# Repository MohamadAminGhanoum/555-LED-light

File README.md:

# 555-LED-light
This project is a type of LED chaser, which is LED's making spinning effect by switching on and off.  i have followed a guide on blueprint, hackclub to build this project.

I think total price is 2 dollar.

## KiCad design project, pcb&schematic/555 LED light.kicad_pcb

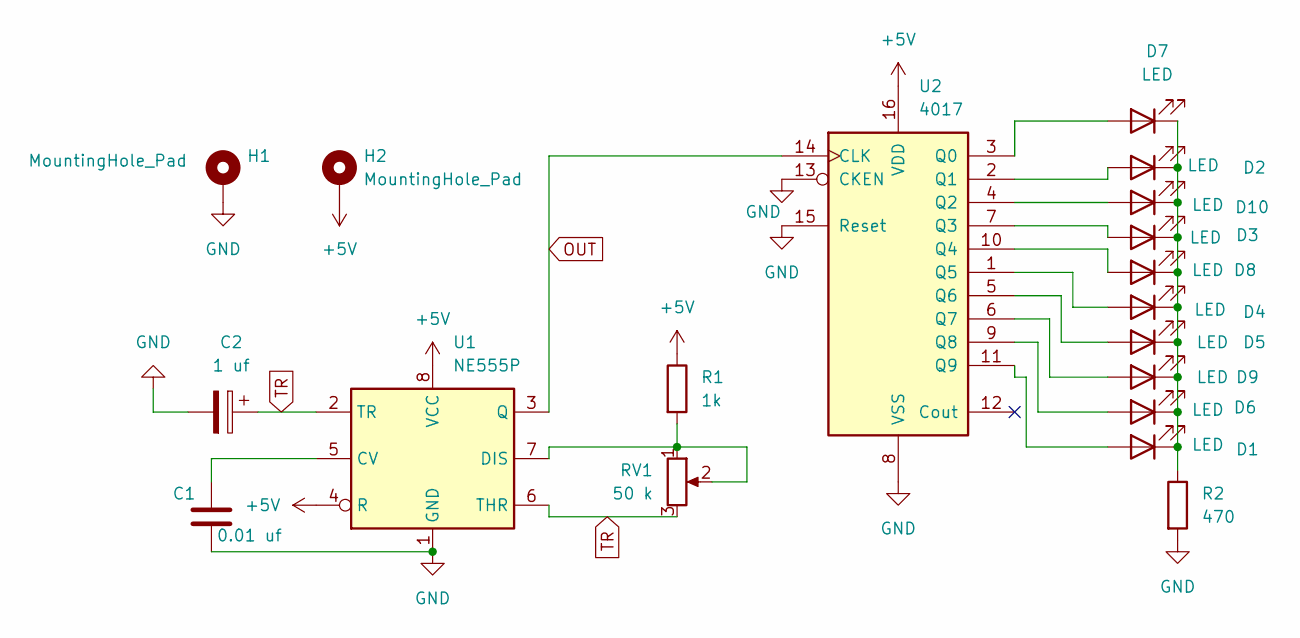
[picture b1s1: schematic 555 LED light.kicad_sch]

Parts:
C1: 0.01 uf; CP_Radial_D5.0mm_P2.00mm
C2: 1 uf; CP_Radial_D5.0mm_P2.00mm
D1, D2, D3, D4, D5, D6, D7, D8, D9, D10: LED; LED_D3.0mm
H1, H2: MountingHole_Pad; PinSocket_1x01_P2.54mm_Vertical
R1: 1k; R_Axial_DIN0207_L6.3mm_D2.5mm_P7.62mm_Horizontal
R2: 470; R_Axial_DIN0207_L6.3mm_D2.5mm_P7.62mm_Horizontal
RV1: 50 k; Potentiometer_Bourns_3296W_Vertical
U1: NE555P; DIP-8_W7.62mm
U2: 4017; N16

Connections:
+5V: H2.1, R1.1, U1.4 (R), U1.8 (VCC), U2.16 (VDD)
GND: C1.2, C2.2, H1.1, R2.2, U1.1 (GND), U2.8 (VSS), U2.13 (CKEN), U2.15 (Reset)
unnamed: D1.2 (A), U2.11 (Q9)
unnamed: D1.1 (K), D2.1 (K), D3.1 (K), D4.1 (K), D5.1 (K), D6.1 (K), D7.1 (K), D8.1 (K), D9.1 (K), D10.1 (K), R2.1
unnamed: D2.2 (A), U2.2 (Q1)
unnamed: D3.2 (A), U2.7 (Q3)
unnamed: D4.2 (A), U2.1 (Q5)
unnamed: D5.2 (A), U2.5 (Q6)
unnamed: D6.2 (A), U2.9 (Q8)
unnamed: D7.2 (A), U2.3 (Q0)
unnamed: D8.2 (A), U2.10 (Q4)
unnamed: D9.2 (A), U2.6 (Q7)
unnamed: D10.2 (A), U2.4 (Q2)
unnamed: C1.1, U1.5 (CV)
unnamed: R1.2, RV1.1, RV1.2, U1.7 (DIS)
OUT: U1.3 (Q), U2.14 (CLK); also elsewhere on the board
TR: C2.1, RV1.3, U1.2 (TR), U1.6 (THR)

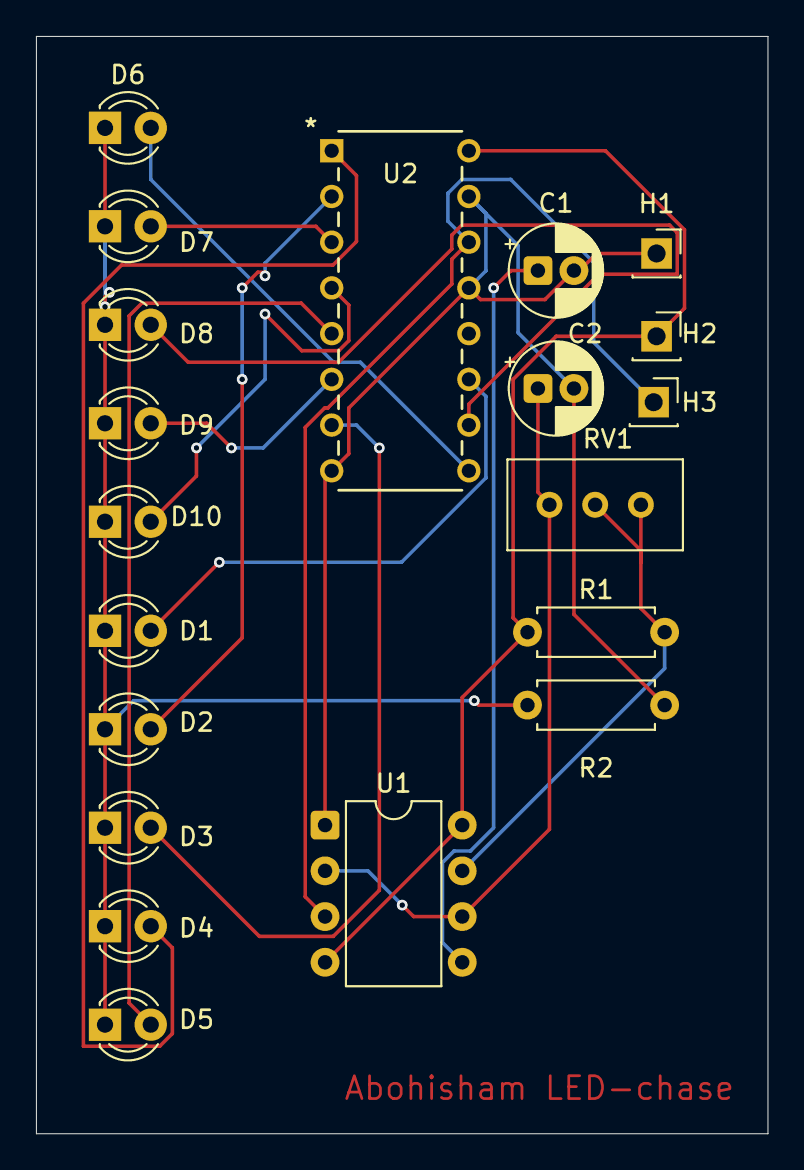
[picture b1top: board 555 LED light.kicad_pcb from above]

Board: 2 copper layers, 40.6 x 61.0 mm, 20 parts (0 on the bottom side), 17 nets.

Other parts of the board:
H3: MountingHole_Pad; PinSocket_1x01_P2.54mm_Vertical

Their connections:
OUT: H3.1; also elsewhere on the board

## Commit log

2025-12-23 Add images to README for LED chaser project
    Added images to illustrate the LED chaser project.
2025-12-27 Rename 555 LED light.kicad_pcb to project, pcb&schematic/555 LED light.kicad_pcb
2025-12-27 Rename Screenshot 2025-12-23 at 11.27.41.png to assets/Screenshot 2025-12-23 at 11.27.41.png
